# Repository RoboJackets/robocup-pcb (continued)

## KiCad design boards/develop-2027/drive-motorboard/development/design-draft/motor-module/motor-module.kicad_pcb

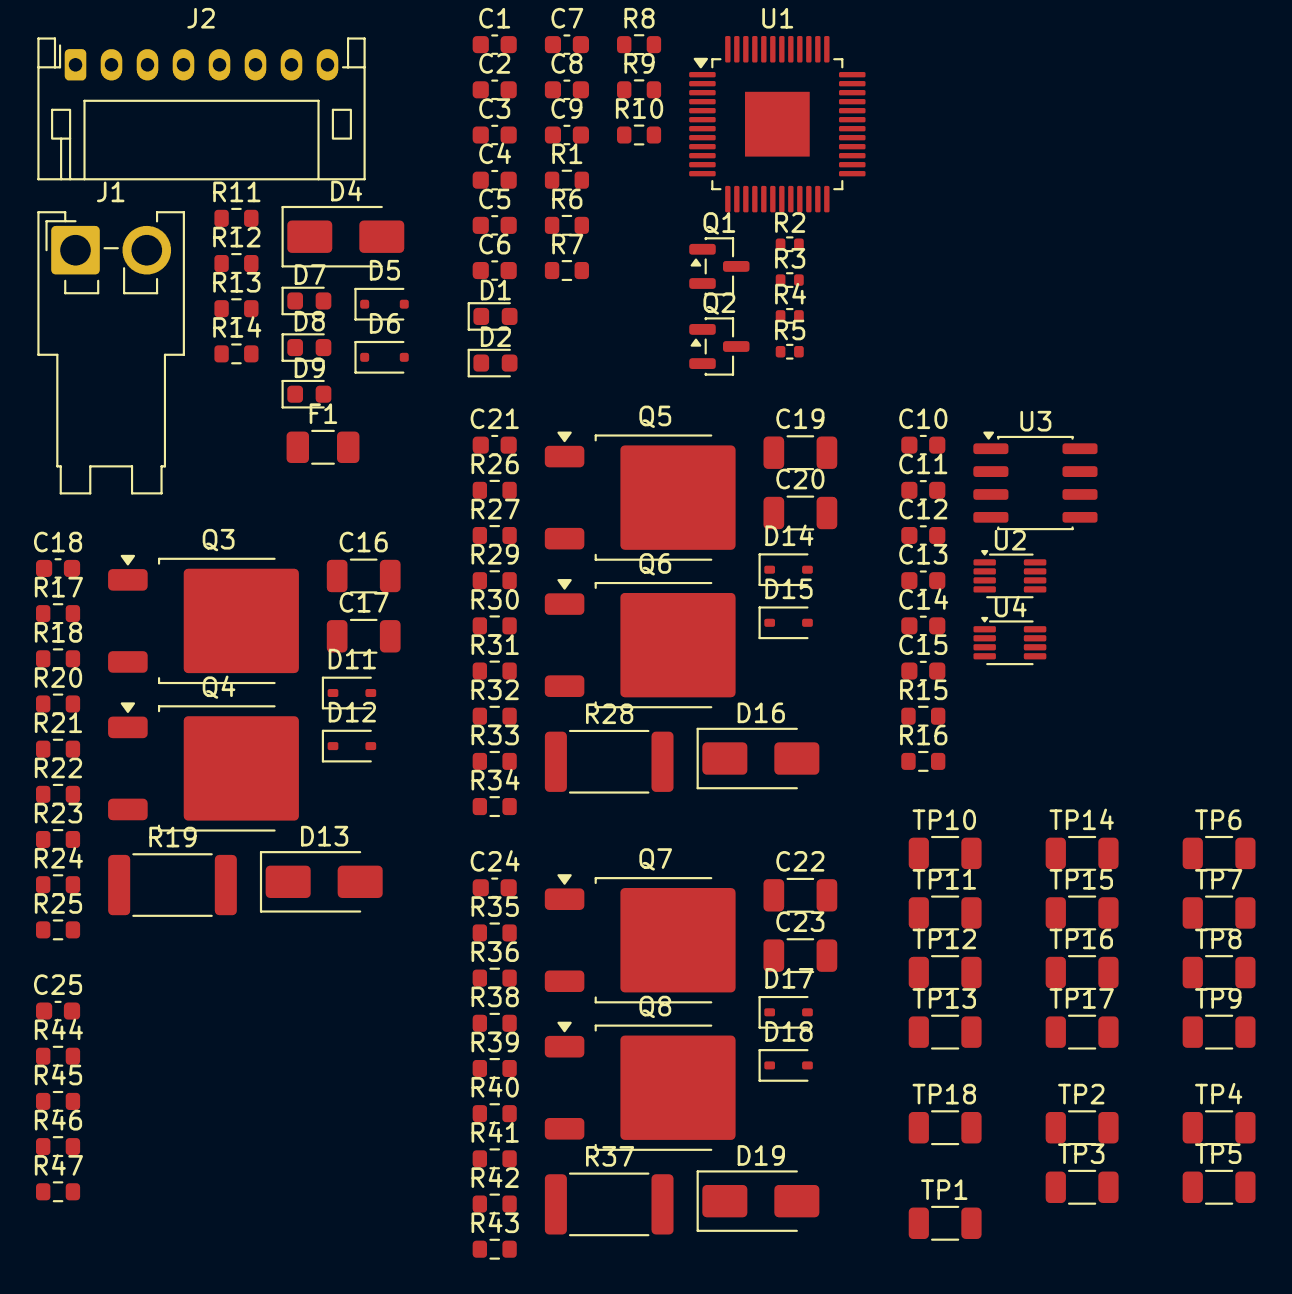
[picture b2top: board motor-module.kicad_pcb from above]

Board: 2 copper layers, 122 parts (0 on the bottom side), 74 nets, no tracks yet.

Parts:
C1, C4, C12, C13, C15: 100n; C_0603_1608Metric
C2, C5, C6, C7, C8, C9: 10u; C_0603_1608Metric
C3, C14: 1u; C_0603_1608Metric
C10, C11: 0.1n; C_0603_1608Metric
C16, C17, C19, C20, C22, C23: 10u; C_1206_3216Metric
C18, C21, C24, C25: 1n; C_0603_1608Metric
D1: FAULT; LED_0603_1608Metric
D2: DEBUG; LED_0603_1608Metric
D4, D13, D16, D19: SMAJ24CA; D_SMA
D5, D6: CUZ5V6,H3F; D_SOD-323F
D7: VDC OK; LED_0603_1608Metric
D8: 5V OK; LED_0603_1608Metric
D9: 3.3V OK; LED_0603_1608Metric
D11, D12, D14, D15, D17, D18: 1N4148WS; D_SOD-323
F1: 12 A 50 V; Fuse_1206_3216Metric
J1: Motor Power In; JST_VH_S2P-VH_1x02_P3.96mm_Horizontal
J2: Logical Conn.; JST_PH_S8B-PH-K_1x08_P2.00mm_Horizontal
Q1, Q2: BSS84AKW,115; SOT-23
Q3, Q4, Q5, Q6, Q7, Q8: STD140N6F7; TO-252-2
R1, R6, R7, R8: 10k; R_0603_1608Metric
R2, R3, R4, R5: 100; R_0402_1005Metric
R9, R10, R11, R12, R13, R14: 1k; R_0603_1608Metric
R15, R16, R17, R18, R25, R26, R27, R34, R35, R36, R43: 100; R_0603_1608Metric
R19, R28, R37: 5m±1% 3W; R_2512_6332Metric
R20, R23, R29, R32, R38, R41: 110±0.1%; R_0603_1608Metric
R21, R22, R30, R31, R39, R40: 6.04k±0.1%; R_0603_1608Metric
R24, R33, R42: 3.01k±0.1%; R_0603_1608Metric
R44, R45, R46: 3.3k; R_0603_1608Metric
R47: 15k; R_0603_1608Metric
TP1: RESET; R_1206_3216Metric
TP2: 5V; R_1206_3216Metric
TP3: 3.3V; R_1206_3216Metric
TP4: ENC_A; R_1206_3216Metric
TP5: ENC_B; R_1206_3216Metric
TP6, TP10, TP14: HS_x; R_1206_3216Metric
TP7, TP11, TP15: LS_x; R_1206_3216Metric
TP8, TP12, TP16: PHASE_x; R_1206_3216Metric
TP9, TP13, TP17: ISENSE_x; R_1206_3216Metric
TP18: OCCOMP; R_1206_3216Metric
U1: STSPIN32G0A2; LQFP-48-1EP_7x7mm_P0.5mm_EP3.6x3.6mm
U2, U4: SN74LVC3G17DCUR; VSSOP-8_2.3x2mm_P0.5mm
U3: SN75157DR; SOIC-8_3.9x4.9mm_P1.27mm

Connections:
+3.3V: C2.2, C3.2, C4.2, C12.1, C15.1, D6.1 (A1), J2.3, Q1.3 (D), Q2.3 (D), R1.1, R7.2, R8.2, R14.1, R21.2, R30.2, R39.2, R47.2, TP3.1, U1.5 (V_{DD}), U2.8 (Vcc), U4.8 (Vcc)
+5V: C13.1, C14.1, D5.1 (A1), J2.1, R13.1, TP2.1, U3.8 (Vcc)
/ENC_A: TP4.1, U1.43 (PB6), U4.7 (1Y)
/ENC_B: TP5.1, U1.45 (PB7), U4.5 (2Y)
/H1: U1.15 (PA3), U2.7 (1Y)
/H2: U1.16 (PA4), U2.5 (2Y)
/H3: U1.17 (PA5), U2.2 (3Y)
/Microcontroller/DEBUG: Q2.1 (G), R7.1, U1.10 (PF0)
/Microcontroller/FAULT: Q1.1 (G), R6.1, U1.1 (PC14)
/Microcontroller/HS_U: D11.1 (K), R17.1, TP6.1, U1.34 (HSU)
/Microcontroller/HS_V: D14.1 (K), R26.1, TP10.1, U1.30 (HSV)
/Microcontroller/HS_W: D17.1 (K), R35.1, TP14.1, U1.26 (HSW)
/Microcontroller/ISENSE_U: R24.2, R25.2, TP9.1, U1.12 (PA0), U1.22 (OP1O)
/Microcontroller/ISENSE_V: R33.2, R34.2, TP13.1, U1.4 (OP2O), U1.20 (PA7)
/Microcontroller/ISENSE_W: R42.2, R43.2, TP17.1, U1.21 (PB1), U1.48 (OP3O)
/Microcontroller/LS_U: D12.1 (K), R18.1, TP7.1, U1.37 (LSU)
/Microcontroller/LS_V: D15.1 (K), R27.1, TP11.1, U1.33 (LSV)
/Microcontroller/LS_W: D18.1 (K), R36.1, TP15.1, U1.29 (LSW)
/Microcontroller/OP_U_N: R23.2, R24.1, U1.23 (OP1N)
/Microcontroller/OP_U_P: R20.2, R21.1, R22.2, U1.24 (OP1P)
/Microcontroller/OP_V_N: R32.2, R33.1, U1.3 (OP2N)
/Microcontroller/OP_V_P: R29.2, R30.1, R31.2, U1.2 (OP2P)
/Microcontroller/OP_W_N: R41.2, R42.1, U1.47 (OP3N)
/Microcontroller/OP_W_P: R38.2, R39.1, R40.2, U1.46 (OP3P)
/Microcontroller/SPI1_CE_USART2_RX: J2.8, R5.1
/Microcontroller/SPI1_MISO: J2.7, R4.1
/Microcontroller/SPI1_MOSI_USART2_TX: J2.6, R3.1
/Microcontroller/SPI1_SCK: J2.5, R2.1
/Microcontroller/~RESET: R8.1, TP1.1, U1.11 (~RST)
/Motor Interface/EN_CH_A: R15.1, U3.1 (1IN+)
/Motor Interface/EN_CH_B: R16.1, U3.6 (2IN+)
/Motor Interface/~EN_CH_A: C10.2, U3.7 (1IN-)
/Motor Interface/~EN_CH_B: C11.2, U3.5 (2IN-)
/OCCOMP: C25.1, R44.2, R45.2, R46.2, R47.1, TP18.1, U1.25 (OCCOMP)
/PHASE_U: C7.1, D13.2 (A2), Q3.3, Q4.1, TP8.1, U1.35 (OUTU)
/PHASE_V: C8.1, D16.2 (A2), Q5.3, Q6.1, TP12.1, U1.31 (OUTV)
/PHASE_W: C9.1, D19.2 (A2), Q7.3, Q8.1, TP16.1, U1.27 (OUTW)
/SHUNT_U: Q4.3, R19.1, R20.1, R44.1
/SHUNT_V: Q6.3, R28.1, R29.1, R45.1
/SHUNT_W: Q8.3, R37.1, R38.1, R46.1
GND: C1.2, C2.1, C3.1, C4.1, C5.1, C6.2, C12.2, C13.2, C14.2, C15.2, C16.2, C17.2, C18.1, C19.2, C20.2, C21.1, C22.2, C23.2, C24.1, C25.2, D1.1 (K), D2.1 (K), D4.1 (A1), D5.2 (A2), D6.2 (A2), D7.1 (K), D8.1 (K), D9.1 (K), D13.1 (A1), D16.1 (A1), D19.1 (A1), J1.2, J2.2, J2.4, R6.2, R19.2, R22.1, R23.1, R28.2, R31.1, R32.1, R37.2, R40.1, R41.1, U1.19 (TESTMODE), U1.44 (GND), U1.49 (GND_PAD), U2.4 (GND), U3.4 (GND), U4.4 (GND)
unnamed: C10.1, R15.2
unnamed: C11.1, R16.2
unnamed: C18.2, R25.1
unnamed: C21.2, R34.1
unnamed: C24.2, R43.1
unnamed: D1.2 (A), R9.2
unnamed: D2.2 (A), R10.2
unnamed: D7.2 (A), R12.2
unnamed: D8.2 (A), R13.2
unnamed: D9.2 (A), R14.2
unnamed: D11.2 (A), Q3.2, R17.2
unnamed: D12.2 (A), Q4.2, R18.2
unnamed: D14.2 (A), Q5.2, R26.2
unnamed: D15.2 (A), Q6.2, R27.2
unnamed: D17.2 (A), Q7.2, R35.2
unnamed: D18.2 (A), Q8.2, R36.2
unnamed: F1.1, J1.1
unnamed: Q1.2 (S), R9.1
unnamed: Q2.2 (S), R10.1
unnamed: R11.2, R12.1
unnamed: R2.2, U1.13 (PA1)
unnamed: R3.2, U1.14 (PA2)
unnamed: R4.2, U1.18 (PA6)
unnamed: R5.2, U1.42 (PA15)
unnamed: C6.1, U1.9 (REG_3V3)
unnamed: C5.2, U1.6 (REG_12V)
unnamed: C7.2, U1.36 (VBOOTU)
unnamed: C8.2, U1.32 (VBOOTV)
unnamed: C9.2, U1.28 (VBOOTW)
unnamed: C1.1, R1.2, U1.38 (~STBY)
unnamed: U3.2 (1OUT), U4.1 (1A)
unnamed: U3.3 (2OUT), U4.3 (2A)
VDC: C16.1, C17.1, C19.1, C20.1, C22.1, C23.1, D4.2 (A2), F1.2, Q3.1, Q5.1, Q7.1, R11.1, U1.7 (VM)

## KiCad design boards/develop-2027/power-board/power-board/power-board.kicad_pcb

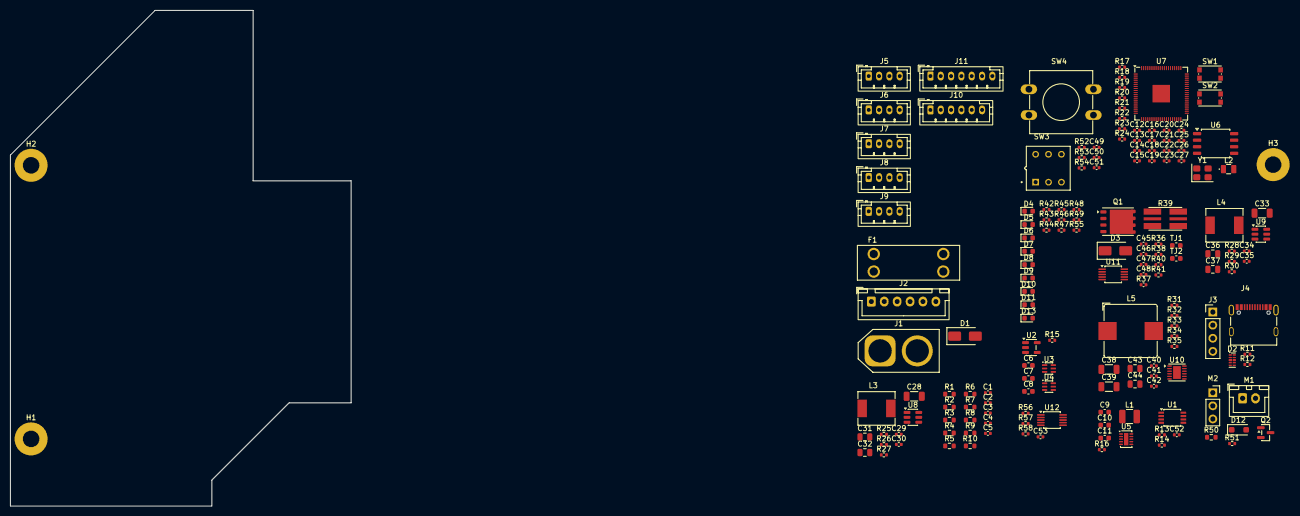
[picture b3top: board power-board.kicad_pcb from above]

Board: 4 copper layers, 66.0 x 96.0 mm, 167 parts (0 on the bottom side), 100 nets, no tracks yet.

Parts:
C1, C2, C3, C4, C5, C12, C15, C16, C18, C20, C21, C22, C23, C25, C26, C27, C49, C50, C51, C52, C53: 100n; C_0402_1005Metric
C6, C9: 1u 63V; C_0603_1608Metric
C7: 1u 25V; C_0603_1608Metric
C8, C10, C11: 10u 25V; C_0603_1608Metric
C13, C14: 15p; C_0402_1005Metric
C17, C19, C24: 4.7u; C_0402_1005Metric
C28, C33, C38, C39: 4.7u 50V; C_1206_3216Metric
C29, C34, C40, C45, C47: 100n 50V; C_0402_1005Metric
C30, C35, C41: 100n 16V; C_0402_1005Metric
C31, C32, C36, C37, C43, C44: 10u 25V; C_0805_2012Metric
C42: 33p; C_0402_1005Metric
C46, C48: 1n; C_0402_1005Metric
D1, D3: SMAJ22CA; D_SMA
D2: PUSB3FR4Z; Diodes_UDFN-10_1x2.5mm_P0.5mm
D4, D5, D6, D7, D8, D9, D10, D11, D13: KT-0603R; LED_0603_1608Metric
D12: SMD110PL-TP; D_SOD-123F
F1: Fuse Holder; Fuseholder_Keystone_3557-2
H1, H2, H3: MountingHole_Pad; MountingHole_3.2mm_M3_Pad
J1: XT60-M; AMASS_XT60-M_1x02_P7.20mm_Vertical
J2: B6B-XH-A; JST_XH_B6B-XH-A_1x06_P2.50mm_Vertical
J3: SWD; PinHeader_1x04_P2.54mm_Vertical
J4: 12402012E212A; USB_C_Receptable_Amphenol_12402012E212A
J5, J6, J7, J8, J9: B4B-PH-K-S; JST_PH_B4B-PH-K_1x04_P2.00mm_Vertical
J10: B6B-PH-K-S; JST_PH_B6B-PH-K_1x06_P2.00mm_Vertical
J11: B7B-PH-K-S; JST_PH_B7B-PH-K_1x07_P2.00mm_Vertical
L1: 10u 540mA; L_1210_3225Metric
L2: 3.3u 2.3A; L_Abracon_AOTA-B201610S
L3: 5.6u 5.5A; L_Bourns_SRP6540
L4: 6.8u 5A; L_Bourns_SRP6540
L5: 6.8u 8A; L_Bourns_SRP1038C_10.0x10.0mm
M1: B2B-XH-A; JST_XH_B2B-XH-A_1x02_P2.50mm_Vertical
M2: Motor_Servo; PinSocket_1x03_P2.54mm_Vertical
Q1: BSC014N06NS; Infineon_PG-TDSON-8_6.15x5.15mm
Q2: 2N7002K; SOT-23
R1: 180k ± 1%; R_0603_1608Metric
R2, R4, R6, R8, R10: 330k ± 1%; R_0603_1608Metric
R3: 1.8M ± 1%; R_0603_1608Metric
R5: 680k ± 1%; R_0603_1608Metric
R7: 2.2M ± 1%; R_0603_1608Metric
R9: 1.2M ± 1%; R_0603_1608Metric
R11, R12: 5.1k; R_0402_1005Metric
R13, R14, R56, R57, R58: 4.7k; R_0402_1005Metric
R15, R20, R21, R22, R35, R41, R42, R43, R44, R45, R46, R47, R48, R49, R53, R55: 1k; R_0402_1005Metric
R16, R23, R24, R25, R28, R31, R36, R51, R52, R54: 100k; R_0402_1005Metric
R17, R18: 27.4; R_0402_1005Metric
R19: 33; R_0402_1005Metric
R26, R29, R33: 100k ± 1%; R_0402_1005Metric
R27: 22.1k ± 1%; R_0402_1005Metric
R30: 13.7k ± 1%; R_0402_1005Metric
R32: 31.6k ± 1%; R_0402_1005Metric
R34: 7.15k ± 1%; R_0402_1005Metric
R37: 41.2k; C_0402_1005Metric
R38: 5.23k; R_0402_1005Metric
R39: 1.5m ± 1% 2W; R_Shunt_Analog_2512_6332_HighAccuracy
R40: 10; R_0402_1005Metric
R50: 100; R_0603_1608Metric
SW1: BOOTSEL; SW_Push_1P1T_NO_CK_KMR2
SW2: RESET; SW_Push_1P1T_NO_CK_KMR2
SW3: TL2201EEYB; SW_E-Switch_TL2201_DPDT
SW4: TL1100F160Q6JBLK; SW_PUSH-12mm
TJ1, TJ2: THJP0603AST1; C_0603_1608Metric
U1: LM75ADP; TSSOP-8_3x3mm_P0.65mm
U2: TLV75533PDBVR; SOT-23-5
U3, U4: LM66100DCK; SOT-363_SC-70-6
U5: TPS62177DQC; WSON-10-1EP_2x3mm_P0.5mm_EP0.84x2.4mm
U6: W25Q16JVSS; SOIC-8_5.3x5.3mm_P1.27mm
U7: RP2350B; QFN-80-1EP_10x10mm_P0.4mm_EP3.4x3.4mm
U8, U9: LMR51430X; SOT-23-6
U10: LMR51450; WSON-12-1EP_3x3mm_P0.5mm_EP1.5x2.5mm
U11: TPS2491DGS; TSSOP-10_3x3mm_P0.5mm
U12: INA226; TSSOP-10_3x3mm_P0.5mm
Y1: ABM8-272-T3; Crystal_SMD_Abracon_ABM8G-4Pin_3.2x2.5mm

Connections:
+1.1V: C15.1, C16.1, C18.1, C24.1, L2.1, U7.10 (DVDD), U7.32 (DVDD), U7.51 (DVDD), U7.65 (VREG_FB)
+3.3V: C8.1, C12.1, C19.1, C20.1, C21.1, C22.1, C23.1, C25.1, C26.1, C27.1, C52.1, C53.1, J3.1, R13.1, R14.1, R19.1, R23.2, R24.2, R56.1, R57.1, R58.1, SW3.6 (C), SW4.1, U1.8 (VCC), U3.6 (VOUT), U4.6 (VOUT), U6.8 (VCC), U7.5 (IOVDD), U7.15 (IOVDD), U7.24 (IOVDD), U7.29 (IOVDD), U7.41 (IOVDD), U7.50 (IOVDD), U7.59 (ADC_AVDD), U7.60 (IOVDD), U7.64 (VREG_VIN), U7.68 (USB_OTP_VDD), U7.69 (QSPI_IOVDD), U7.76 (IOVDD), U12.6 (VS)
/Battery Connectors/Batt_Balance.Cell0: C1.1, R1.2, R2.1, U7.54 (GPIO43/ADC3)
/Battery Connectors/Batt_Balance.Cell1: C3.1, R5.2, R6.1, U7.55 (GPIO44/ADC4)
/Battery Connectors/Batt_Balance.Cell2: C5.1, R9.2, R10.1, U7.56 (GPIO45/ADC5)
/Battery Connectors/Batt_Balance.Cell3: C2.1, R3.2, R4.1, U7.58 (GPIO47/ADC7)
/Battery Connectors/Batt_Balance.Cell4: C4.1, R7.2, R8.1, U7.57 (GPIO46/ADC6)
/Battery Connectors/Batt_Cell0: J2.5, R1.1
/Battery Connectors/Batt_Cell1: J2.4, R5.1
/Battery Connectors/Batt_Cell2: J2.3, R9.1
/Battery Connectors/Batt_Cell3: J2.2, R3.1
/Battery Connectors/Batt_Cell4: J2.1, R7.1
/Battery Connectors/VBATT: C9.1, C45.1, D1.1 (A1), F1.2, R39.3, R39.4, TJ1.1 (Pin1), U5.2 (VIN), U5.3 (EN), U11.10 (VCC), U12.10 (Vin+)
/MCU Connectors/CC1: J4.B5 (CC1_B), R11.1
/MCU Connectors/CC2: J4.A5 (CC1_A), R12.1
/MCU Connectors/CLK: J3.3, U7.33 (SWCLK)
/MCU Connectors/DN: D2.1 (CH1), J4.A7 (D-_A), J4.B7 (D-_B), R17.1
/MCU Connectors/DP: D2.5 (CH4), J4.A6 (D+_A), J4.B6 (D+_B), R18.1
/MCU Connectors/IO: J3.2, U7.34 (SWDIO)
/MCU Power/3.3V_MCU_BUCK: C10.1, C11.1, L1.2, R15.1, R16.1, U3.1 (VIN), U5.8 (~SLEEP), U5.10 (VOS)
/MCU Power/3.3V_USB: C7.1, U2.5 (OUT), U3.3 (~CE), U4.1 (VIN)
/MCU/3.3V_EN: R25.1, U7.25 (GPIO24), U8.5 (EN)
/MCU/5.0V_EN: R28.1, U7.23 (GPIO23), U9.5 (EN)
/MCU/12.0V_EN: R31.1, U7.22 (GPIO22), U10.9 (EN)
/MCU/CURR_ALERT: R58.2, U7.11 (GPIO12), U12.3 (~Alert)
/MCU/ESTOP: C51.1, R52.1, SW3.5 (B), U7.13 (GPIO14)
/MCU/FAN_PWM: R50.1, U7.9 (GPIO11)
/MCU/IND_3.3V_EN: D7.2 (A), U7.80 (GPIO3)
/MCU/IND_5V_EN: D6.2 (A), U7.79 (GPIO2)
/MCU/IND_12V_EN: D5.2 (A), U7.78 (GPIO1)
/MCU/IND_COOL_CH1: D8.2 (A), U7.1 (GPIO4)
/MCU/IND_COOL_CH2: D9.2 (A), U7.2 (GPIO5)
/MCU/IND_ESTOP: D10.2 (A), U7.7 (GPIO9)
/MCU/IND_OVERTEMP: D11.2 (A), U7.4 (GPIO7)
/MCU/IND_SYSTEM: D13.2 (A), U7.6 (GPIO8)
/MCU/IND_VBATT_EN: D4.2 (A), U7.77 (GPIO0)
/MCU/POWERSW: C49.1, R53.2, U7.12 (GPIO13)
/MCU/QSPI_CLK: U6.6 (CLK), U7.71 (QSPI_SCLK)
/MCU/QSPI_SD0: U6.5 (DI/IO_{0}), U7.72 (QSPI_SD0)
/MCU/QSPI_SD1: U6.2 (DO/IO_{1}), U7.74 (QSPI_SD1)
/MCU/QSPI_SD2: U6.3 (~WP/IO_{2}), U7.73 (QSPI_SD2)
/MCU/QSPI_SD3: U6.7 (~HOLD/~RESET/IO_{3}), U7.70 (QSPI_SD3)
/MCU/RX: J11.1, U7.19 (GPIO19)
/MCU/SCL: R14.2, R57.2, U1.2 (SCL), U7.17 (GPIO17), U7.28 (GPIO27), U12.5 (SCL)
/MCU/SDA: R13.2, R56.2, U1.1 (SDA), U7.16 (GPIO16), U7.27 (GPIO26), U12.4 (SDA)
/MCU/SERVO_PWM: M2.1 (PWM), U7.8 (GPIO10)
/MCU/TX: J11.2, U7.18 (GPIO18)
/MCU/VBATT_EN: SW3.1 (A), U7.26 (GPIO25)
/MCU/~BOOTSEL: R21.2, R23.1, U6.1 (~CS), U7.75 (~QSPI_SS)
/MCU/~RESET: R22.2, R24.1, U7.35 (RUN)
/Output Connectors/3.3V_REG: C31.1, C32.1, J11.4, L3.2, R26.1
/Output Connectors/5.0V_REG: C36.1, C37.1, D12.1 (K), J11.6, L4.2, M1.1 (+), M2.2 (+), R29.1
/Output Connectors/12.0V_REG: C43.1, C44.1, J10.4, J10.5, J10.6, L5.2, R33.1, R35.1
/Output Power Stage/25V, 30A Load Switch/SHUNT_L: Q1.5 (D), R39.1, R39.2, U11.9 (SENSE), U12.8 (Vbus), U12.9 (Vin-)
/Output Power Stage/LOADSW_EN: C50.1, R36.1, SW3.2 (B), U11.1 (EN)
GND: C1.2, C2.2, C3.2, C4.2, C5.2, C6.2, C7.2, C8.2, C9.2, C10.2, C11.2, C12.2, C13.1, C14.1, C15.2, C16.2, C17.2, C18.2, C19.2, C20.2, C21.2, C22.2, C23.2, C24.2, C25.2, C26.2, C27.2, C28.2, C29.2, C31.2, C32.2, C33.2, C34.2, C36.2, C37.2, C38.2, C39.2, C40.2, C42.2, C43.2, C44.2, C45.2, C46.2, C47.2, C48.2, C49.2, C50.2, C51.2, C52.2, C53.2, D1.2 (A2), D2.3 (GND), D2.8 (GND), D3.2 (A2), H1.1 (1_1), H2.1 (1_1), H3.1 (1_1), J1.1, J2.6, J3.4, J4.A1_B12 (GND), J4.B1_A12 (GND), J4.SH1 (SHIELD), J4.SH2 (SHIELD), J4.SH3 (SHIELD), J4.SH4 (SHIELD), J5.1, J5.2, J6.1, J6.2, J7.1, J7.2, J8.1, J8.2, J9.1, J9.2, J10.1, J10.2, J10.3, J11.3, J11.5, J11.7, M2.3 (-), Q2.2 (S), R2.2, R4.2, R6.2, R8.2, R10.2, R11.2, R12.2, R25.2, R27.2, R28.2, R30.2, R31.2, R32.2, R34.2, R36.2, R38.2, R42.2, R43.2, R44.2, R45.2, R46.2, R47.2, R48.2, R49.2, R51.2, R52.2, R54.2, R55.2, SW1.1 (A), SW2.1 (A), SW3.3 (C), SW3.4 (A), TJ1.2 (Pin2), TJ2.1 (Pin1), U1.4 (GND), U1.5 (A2), U1.6 (A1), U1.7 (A0), U2.2 (GND), U3.2 (GND), U4.2 (GND), U4.5 (ST), U5.1 (PGND), U5.4 (NC), U5.5 (FB), U5.6 (AGND), U5.11 (PAD), U6.4 (GND), U7.62 (VREG_PGND), U7.81 (GND), U8.1 (GND), U9.1 (GND), U10.5 (PG), U10.8 (AGND), U10.13 (PGND), U11.5 (GND), U11.6 (PG), U12.1 (A1), U12.2 (A0), U12.7 (GND), Y1.2 (G), Y1.4 (G)
unnamed: C14.2, R20.1, Y1.3
unnamed: C41.2, L5.1, U10.1 (SW), U10.2 (SW), U10.3 (SW)
unnamed: C42.1, R35.2
unnamed: C48.1, R41.2
unnamed: D4.1 (K), R42.1
unnamed: D5.1 (K), R43.1
unnamed: D6.1 (K), R44.1
unnamed: D7.1 (K), R45.1
unnamed: D8.1 (K), R46.1
unnamed: D9.1 (K), R47.1
unnamed: D10.1 (K), R48.1
unnamed: D11.1 (K), R49.1
unnamed: D12.2 (A), M1.2 (-), Q2.3 (D)
unnamed: D13.1 (K), R55.1
unnamed: F1.1, J1.2
unnamed: Q1.4 (G), R40.1
unnamed: Q2.1 (G), R50.2, R51.1
unnamed: R53.1, R54.1, SW4.2
unnamed: R21.1, SW1.2 (B)
unnamed: R22.1, SW2.2 (B)
unnamed: R15.2, U3.5 (ST), U4.3 (~CE)
unnamed: R16.2, U5.7 (PG)
unnamed: L1.1, U5.9 (SW)
unnamed: R17.2, U7.66 (USB_DM)
unnamed: R18.2, U7.67 (USB_DP)
unnamed: C17.1, R19.2, U7.61 (VREG_AVDD)
unnamed: L2.2, U7.63 (VREG_LX)
unnamed: C13.2, U7.30 (XIN), Y1.1
unnamed: R20.2, U7.31 (XOUT)
unnamed: C30.1, U8.6 (CB)
unnamed: R26.2, R27.1, U8.4 (FB)
unnamed: C30.2, L3.1, U8.2 (SW)
unnamed: C35.1, U9.6 (CB)
unnamed: R29.2, R30.1, U9.4 (FB)
unnamed: C35.2, L4.1, U9.2 (SW)
unnamed: C41.1, U10.4 (BOOT)
unnamed: R33.2, R34.1, U10.7 (FB)
unnamed: R32.1, U10.6 (RT)
unnamed: R40.2, R41.1, U11.8 (GATE)
unnamed: R37.2, R38.1, U11.3 (PROG)
unnamed: C46.1, U11.4 (TIMER)
unnamed: R37.1, U11.2 (VREF)
VBUS: C6.1, J4.A4_B9 (VBUS), J4.B4_A9 (VBUS), U2.1 (IN), U2.3 (EN)
VIN: C28.1, C29.1, C33.1, C34.1, C38.1, C39.1, C40.1, C47.1, D3.1 (A1), J5.3, J5.4, J6.3, J6.4, J7.3, J7.4, J8.3, J8.4, J9.3, J9.4, Q1.1 (S), Q1.2 (S), Q1.3 (S), TJ2.2 (Pin2), U8.3 (VIN), U9.3 (VIN), U10.10 (VIN), U10.11 (VIN), U10.12 (VIN), U11.7 (OUT)

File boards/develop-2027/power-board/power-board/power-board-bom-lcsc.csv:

"Reference","Qty","Value","Manufacturer P/N","Vendor","Vendor P/N"
"SW1","1","BOOTSEL","KMR211G LFS","LCSC","C99271"
"SW2","1","RESET","KMR211G LFS","LCSC","C99271"
"C1,C2,C3,C4,C5,C12,C15,C16,C18,C20,C21,C22,C23,C25,C26,C27","16","100n","GCM155R71H104KE02D","LCSC","C85858"
"C13,C14","2","15p","GJM1555C1H150GB01D","LCSC","C440152"
"C17,C19,C24","3","4.7u","GRM155R60J475ME47D","LCSC","C82453"
"C29,C34,C40,C45,C47","5","100n 50V","GCM155R71H104KE02D","LCSC","C85858"
"C30,C35,C41","3","100n 16V","GCM155R71H104KE02D","LCSC","C85858"
"C42","1","33p","GCM1555C1H330JA16D","LCSC","C126506"
"C46,C48","2","1n","GCM155R71H102KA37D","LCSC","C126532"
"R37","1","41.2k","0402WGF4122TCE","LCSC","C26978"
"C6,C9","2","1u 63V","CL10B105KB8NQNC","LCSC","C5199872"
"C7","1","1u 25V","CL10B105KB8NQNC","LCSC","C5199872"
"C8,C10,C11","3","10u 25V","GRM188R6YA106MA73D","LCSC","C91606"
"C31,C32,C36,C37","4","10u 16V","GRM21BR61E106MA73L","LCSC","C15850"
"C43,C44","2","10u 25V","GRM21BR61E106MA73L","LCSC","C15850"
"C28,C33,C38,C39","4","4.7u 50V","GRM31CR71H475KA12L","LCSC","C77096"
"J1","1","XT60-M","XT60-M.","LCSC","C98733"
"J5,J6,J7,J8,J9","5","B4B-PH-K-S","B4B-PH-K-S","LCSC","C131334"
"J10","1","B6B-PH-K-S","B6B-PH-K-S","LCSC","C131342"
"J11","1","B7B-PH-K-S","C157981","LCSC","C157981"
"J13","1","B2B-XH-A","B2B-XH-A","LCSC","C158012"
"J2","1","B6B-XH-A","B6B-XH-A","LCSC","C144397"
"Y1","1","ABM8-272-T3","ABM8-272-T3","LCSC","C20625731"
"D1,D3","2","SMAJ22CA","SMAJ22CA","LCSC","C148221"
"D12","1","SMD110PL-TP","SMD110PL-TP","LCSC","C669053"
"L1","1","10u 540mA","LBC3225T100KR","LCSC","C223424"
"L5","1","6.8u 8A","SRP1038A-6R8M","LCSC","C2047223"
"D4,D5,D6,D7,D8,D9,D10,D11","8","KT-0603R","KT-0603R","LCSC","C2286"
"D2","1","PUSB3FR4Z","PUSB3FR4Z","LCSC","C503418"
"U7","1","RP2350B","RP2350B","LCSC","C42415655"
"U6","1","W25Q16JVSS","W25Q16JVSSIQ","LCSC","C131025"
"U11","1","TPS2491DGS","TPS2491DGS","LCSC","C273636"
"U1","1","LM75ADP","LM75ADP,118","LCSC","C843694"
"Q1","1","BSC014N06NS","BSC014N06NSATMA1","LCSC","C113391"
"U5","1","TPS62177DQC","TPS62177DQC","LCSC","C91241"
"U10","1","LMR51450","LMR51450FNDRRR","LCSC","C5782413"
"Q2","1","2N7002K","2N7002K-TP","LCSC","C77975"
"U2","1","TLV75533PDBVR","TLV75533PDBVR","LCSC","C404027"
"U8,U9","2","LMR51430X","LMR51430XDDCR","LCSC","C5185863"
"U3,U4","2","LM66100DCK","LM66100DCKR","LCSC","C2869734"
"R11,R12","2","5.1k","RC0402FR-075K1L","LCSC","C105872"
"R13,R14","2","4.7k","RC0402FR-074K7L","LCSC","C105871"
"R15,R20,R21,R22,R35,R41,R42,R43,R44,R45,R46,R47,R48,R49","14","1k","RC0402FR-071KL","LCSC","C106235"
"R16,R23,R24,R25,R28,R31,R36,R51","8","100k","RC0402FR-07100KL","LCSC","C60491"
"R17,R18","2","27.4","RC0402FR-0727R4L","LCSC","C3951825"
"R19","1","33","RC0402JR-0733RL","LCSC","C137880"
"R26,R29,R33","3","100k ± 1%","RC0402FR-07100KL","LCSC","C60491"
"R27","1","22.1k ± 1%","RMCF0402FT22K1","LCSC","C226356"
"R30","1","13.7k ± 1%","RC0402FR-0713K7L","LCSC","C274888"
"R32","1","31.6k ± 1%","RC0402FR-0731K6L","LCSC","C11463"
"R34","1","7.15k ± 1%","RC0402FR-077K15L","LCSC","C409927"
"R38","1","5.23k","RC-02K243JT","LCSC","C1152"
"R40","1","10","RC0402FR-0710RL","LCSC","C138066"
"R1","1","180k ± 1%","CR0603-FX-1803ELF","LCSC","C123419"
"R2,R4,R6,R8,R10","5","330k ± 1%","MCR03SEQPF3303","LCSC","C114618"
"R3","1","1.8M ± 1%","RC0603FR-071M8L","LCSC","C13318"
"R5","1","680k ± 1%","MCR03SEQPF6803","LCSC","C137690"
"R7","1","2.2M ± 1%","RC0603FR-072M2L","LCSC","C22938"
"R9","1","1.2M ± 1%","RC0603FR-131M2L","LCSC","C137774"
"R50","1","100","CRCW0603100RFKEA","LCSC","C844917"
"J4","1","12402012E212A","12402012E212A","LCSC","C5150972"
"L2","1","3.3u 2.3A","AOTA-B201610S3R3-101-T","LCSC","C42411119"
"L3","1","5.6u 5.5A","SRP6540-5R6M","LCSC","C2041376"
"L4","1","6.8u 5A","SRP6540-6R8M","LCSC","C2041325"
"R39","1","1.5m ± 1% 2W","PA2512FKF7W1U5E","LCSC","C7023721"

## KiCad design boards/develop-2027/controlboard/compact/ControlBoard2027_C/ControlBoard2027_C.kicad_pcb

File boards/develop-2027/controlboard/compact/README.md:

# Compact board set (ControlBoard2027_C + 30 x 40 radio)

The compact set is the active 2027 robot electronics design: a 120 x 60 mm controlboard with an STM32H723 and a
30 x 40 mm ESP32-C5 radio that plugs straight onto it. It replaces the prototype set in `../prototype/` (kept for
reference only); every difference is listed in [docs/PROTOTYPE_TO_COMPACT.md](docs/PROTOTYPE_TO_COMPACT.md).

| Board | Folder | Size, layers | Main parts |
|---|---|---|---|
| ControlBoard2027_C | [ControlBoard2027_C/](ControlBoard2027_C/) | 120 x 60 mm, 6 layers, JLC06161H-3313E 1.6 mm | STM32H723ZGT6, LSM6DSV320X IMU, microSD, USB-C, 4 motor + dribbler SPI ports, kicker / expansion I2C, powerboard input, DotStar LEDs, OLED socket |
| RadioBoard2027_C_Inboard | [RadioBoard2027_C_Inboard/](RadioBoard2027_C_Inboard/) | 30 x 40 mm, 4 layers, JLC04161H-3313 1.6 mm | ESP32-C5-WROOM-1U, USB-C, power mux + supervisor |
| RadioBoard2027_C_Overhang | [RadioBoard2027_C_Overhang/](RadioBoard2027_C_Overhang/) | 30 x 40 mm, 4 layers, JLC04161H-3313 1.6 mm | same circuit as Inboard |

## Which files are authoritative

1. The KiCad files in each board folder (`.kicad_sch`, `.kicad_pcb`, `.kicad_dru`, `lib/`, `footprints/`). They
   always win.
2. The documents below, which were checked against those files on 2026-11-07.

Positions in all documents are in mm from the top-left corner of the board's own outline, x right, y down. In the
board files that corner is at (49.475, 49.475) on the controlboard and (97.0, 100.0) on the radios.

| Document | For | Content |
|---|---|---|
| [docs/INTERFACE.md](docs/INTERFACE.md) | everyone | J9 / J2 board-to-board pin table, mating rule, positions, standoffs, stack height, keep-outs, link timing; controlboard external connector pinouts and what mating boards must use |
| [docs/FIRMWARE.md](docs/FIRMWARE.md) | firmware | STM32 and ESP32-C5 pin maps, clocks, GPIO speed rules, IMU orientation, power switchover, bring-up checklist |
| [docs/PROTOTYPE_TO_COMPACT.md](docs/PROTOTYPE_TO_COMPACT.md) | reviewers, firmware | every change from the prototype, part by part, with reasons |
| [ControlBoard2027_C/DESIGN_NOTES.md](ControlBoard2027_C/DESIGN_NOTES.md), [TODO.txt](ControlBoard2027_C/TODO.txt) | reviewers | controlboard design reasoning, stackup, lengths, rules, deviations; open items |
| [RadioBoard2027_C_Inboard/DESIGN_NOTES.md](RadioBoard2027_C_Inboard/DESIGN_NOTES.md), [TODO.txt](RadioBoard2027_C_Inboard/TODO.txt) | reviewers | Inboard radio design notes; open items |
| [RadioBoard2027_C_Overhang/DESIGN_NOTES.md](RadioBoard2027_C_Overhang/DESIGN_NOTES.md), [TODO.txt](RadioBoard2027_C_Overhang/TODO.txt) | reviewers | Overhang radio design notes; open items |

Diagrams:
- [docs/img/interface_stack.svg](docs/img/interface_stack.svg): the set from above, connectors, J9 pin map, stack;
- [docs/img/cb_compact_layout_top.svg](docs/img/cb_compact_layout_top.svg) and
  [docs/img/cb_compact_layout_bottom.svg](docs/img/cb_compact_layout_bottom.svg): controlboard placement by function;
- [RadioBoard2027_C_Inboard/docs/board_map.svg](RadioBoard2027_C_Inboard/docs/board_map.svg) and
  [RadioBoard2027_C_Overhang/docs/board_map.svg](RadioBoard2027_C_Overhang/docs/board_map.svg): radio buttons, LEDs,
  USB, test pads and the J2 pin map.

## BOM

The bills of materials are in each board's `bom/` folder: [ControlBoard2027_C/bom/](ControlBoard2027_C/bom/),
[RadioBoard2027_C_Inboard/bom/](RadioBoard2027_C_Inboard/bom/) and
[RadioBoard2027_C_Overhang/bom/](RadioBoard2027_C_Overhang/bom/). Each folder has a full BOM with sourcing and stock,
the JLCPCB upload file, a list of the parts to order separately (Digi-Key / Mouser), and a README with the stock date,
board-set limits, substitutions and open issues. The JLCPCB upload file is generated from the schematic fields.
The LDOs (CB U7, radio U4) are Microchip MCP1826S-3302E/DB (the AP7361C-33E-13 was out of stock everywhere on
2026-11-07). The LSHM mezzanine (CB J9, radio J2) is JLCPCB-assembled as C3643542: 37 at JLCPCB on 2026-11-07, two
per board set, so 18 board sets.

## Folder map

| Path | Content |
|---|---|
| `README.md` | this file |
| `docs/` | set-level documents; `docs/img/` their SVG diagrams |
| `ControlBoard2027_C/` | controlboard KiCad project, `DESIGN_NOTES.md`, `TODO.txt`, `lib/`, `footprints/` |
| `RadioBoard2027_C_Inboard/` | Inboard radio KiCad project, `DESIGN_NOTES.md`, `TODO.txt`, `docs/board_map.svg`, `lib/` |
| `RadioBoard2027_C_Overhang/` | Overhang radio KiCad project, `DESIGN_NOTES.md`, `TODO.txt`, `docs/board_map.svg`, `lib/` |

## The two radio variants

Both radios have the same schematic (identical netlists), the same outline, the same J2 position and pinout and the
same standoff holes, so either one fits the same controlboard. Both accept the ESP32-C5-WROOM-1U (primary build,
u.FL connector with an external antenna) and the ESP32-C5-WROOM-1 (fallback, PCB antenna) on one dual footprint.
They differ only in where the module sits, which matters only for a WROOM-1 build:

| | Inboard | Overhang |
|---|---|---|
| Module position | (19.85, 17.9), antenna end 1 mm inside the north edge | (19.85, 11.5), antenna end past the north edge |
| WROOM-1 antenna | inside the radio outline, over the controlboard (CB x 46.1-66.1, y 0-7.5, where the CB has copper) | 5.45 mm past the radio and controlboard front edge (keep-out 6.4 mm) |
| Link length on the radio (matched) | 19.934 mm | 14.079 mm |
| USB pair skew | orientation B -0.001 mm, A +5.94 mm (about 40 ps; a both-orientation match does not fit beside SW2; negligible at Full Speed; one-orientation match accepted per the user's instruction) | -0.001 / +0.000 mm in both orientations |
| Buttons | RESET on the west edge, BOOT on the south edge | RESET and BOOT side by side near the south edge |

With the WROOM-1U both variants work the same. Pick the Overhang if a WROOM-1 build is likely and the robot has room
in front of the board; pick the Inboard if nothing may stick out.

## Status (2026-11-07)

All three boards are placed and routed. Checks on the saved repo files (kicad-cli, schematic parity on, zones as
saved):

| Board | DRC errors | Unconnected | Parity | DRC warnings | ERC |
|---|---|---|---|---|---|
| ControlBoard2027_C | 0 | 0 | 0 | 13, all intended: 11 courtyard overlaps (J9 / U2 margin 0.02 mm; ten low parts under the raised OLED module J13) and 2 J2 locating holes under J13 | 1 error, intended: U2 VCAP pins 71 / 106 tied (power output to power output) |
| RadioBoard2027_C_Inboard | 0 | 0 | 0 | 0 | 0 |
| RadioBoard2027_C_Overhang | 0 | 0 | 0 | 0 | 0 |

Matched groups (re-measured with the length scripts on the saved boards):

| Group | Result |
|---|---|
| CB radio SPI3 (to J9) | 14.860-14.861 mm |
| CB SDMMC2 | 62.231-62.496 mm (D1 +0.264 mm, within 1 mm) |
| CB motor SPI1 / SPI2 / dribbler SPI4, LED SPI6 | each connector within 0.001 mm, except J6 MOSI -0.222 mm |
| CB USB | 0.000 mm skew in both plug orientations |
| Radio link SCK / MOSI / MISO / CS | Inboard 19.934 mm, Overhang 14.079 mm, spread 0.000 mm |
| Radio USB | see the variant table above |

Each board's independent adversarial audits are summarised in the Review history appendix of its DESIGN_NOTES.

### Open before ordering

Details and the full lists are in each board's TODO.txt.

- **All boards:** confirm the impedance widths in JLC's calculator and order with impedance control; independent
  re-audit of the last changed areas (CB back-edge connectors and audit fixes; Overhang USB-skew changes; Inboard
  after any further change), then refill zones, DRC with parity, ERC and the length scripts again; generate the
  placement files (the BOMs exist, see above); re-check stock (LSHM C3643542 is the limiting JLCPCB part); parts not
  stocked at JLCPCB must be sourced and consigned (CB: D7-D11, U11; radios: U1, ANT1).
- **Controlboard:** agree J15 (powerboard), J10 (kicker) and J4-J8 (motor modules: their connector is still PH 8P)
  pinouts with the mating boards; choose the OLED module; confirm the DotStar footprint (top-view drawing).
- **Radios:** decide the antenna (FXP831 5 GHz gain above the module's certified gain; Inboard WROOM-1 fallback sits
  over CB copper); fab notes for tented and plugged vias and the J2 paste-in-hole stencil; check the TPD4E05U06 land
  pattern against TI's drawing.

Fabrication outputs (gerbers, CPL) are not generated for the compact set; the BOMs are in each board's `bom/`.

## Interface rule

J9 / J2 and the standoff holes are shared by three projects. Change them in all three together and re-run the
mating check; see [docs/INTERFACE.md](docs/INTERFACE.md) §6.

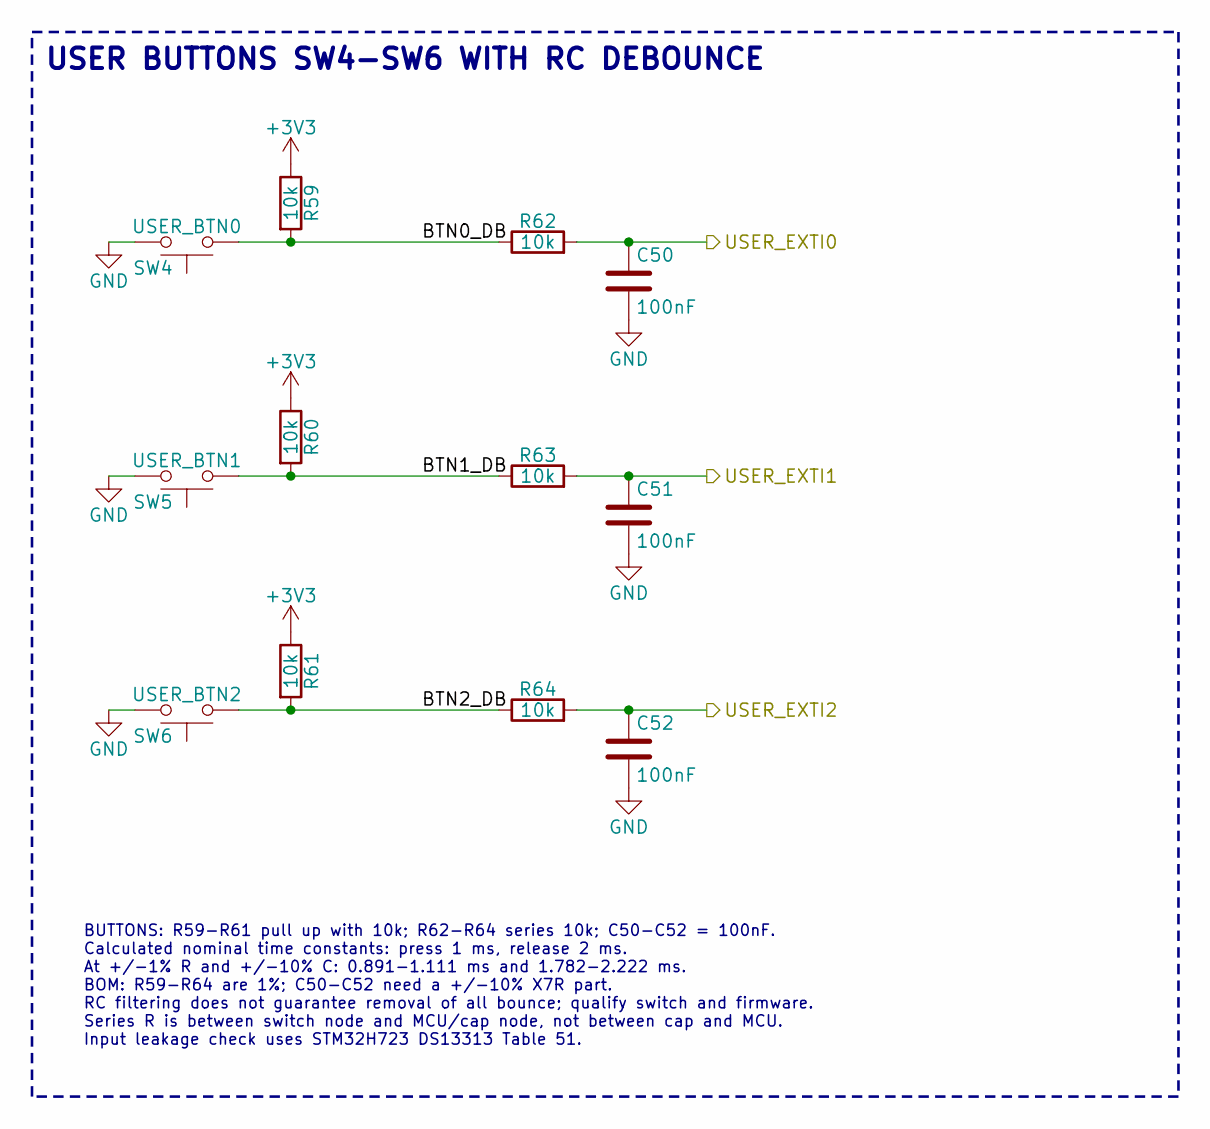
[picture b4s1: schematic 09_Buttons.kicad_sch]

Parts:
C50, C51, C52: 100nF; C_0402_1005Metric; Rating 16V X7R; MPN Samsung CL05B104KO5NNNC; LCSC C1525
R59, R60, R61, R62, R63, R64: 10k; R_0603_1608Metric; Rating 1%; MPN Panasonic ERJ-3EKF1002V; LCSC C25804
SW4: USER_BTN0; SW_PUSH_1P1T_6x3.5mm_H4.3_APEM_MJTP1243; MPN APEM MJTP1243; LCSC C2689636
SW5: USER_BTN1; SW_PUSH_1P1T_6x3.5mm_H4.3_APEM_MJTP1243; MPN APEM MJTP1243; LCSC C2689636
SW6: USER_BTN2; SW_PUSH_1P1T_6x3.5mm_H4.3_APEM_MJTP1243; MPN APEM MJTP1243; LCSC C2689636

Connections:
+3V3: R59.1, R60.1, R61.1; also elsewhere on the board
/MCU/USER_EXTI0: C50.1, R62.2; also elsewhere on the board
/MCU/USER_EXTI1: C51.1, R63.2; also elsewhere on the board
/MCU/USER_EXTI2: C52.1, R64.2; also elsewhere on the board
/User Buttons/BTN0_DB: R59.2, R62.1, SW4.1
/User Buttons/BTN1_DB: R60.2, R63.1, SW5.1
/User Buttons/BTN2_DB: R61.2, R64.1, SW6.1

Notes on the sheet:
BUTTONS: R59-R61 pull up with 10k; R62-R64 series 10k; C50-C52 = 100nF. Calculated nominal time constants: press 1 ms, release 2 ms. At +/-1% R and +/-10% C: 0.891-1.111 ms and 1.782-2.222 ms. BOM: R59-R64 are 1%; C50-C52 need a +/-10% X7R part. RC filtering does not guarantee removal of all bounce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
USER BUTTONS SW4-SW6 WITH RC DEBOUNCE

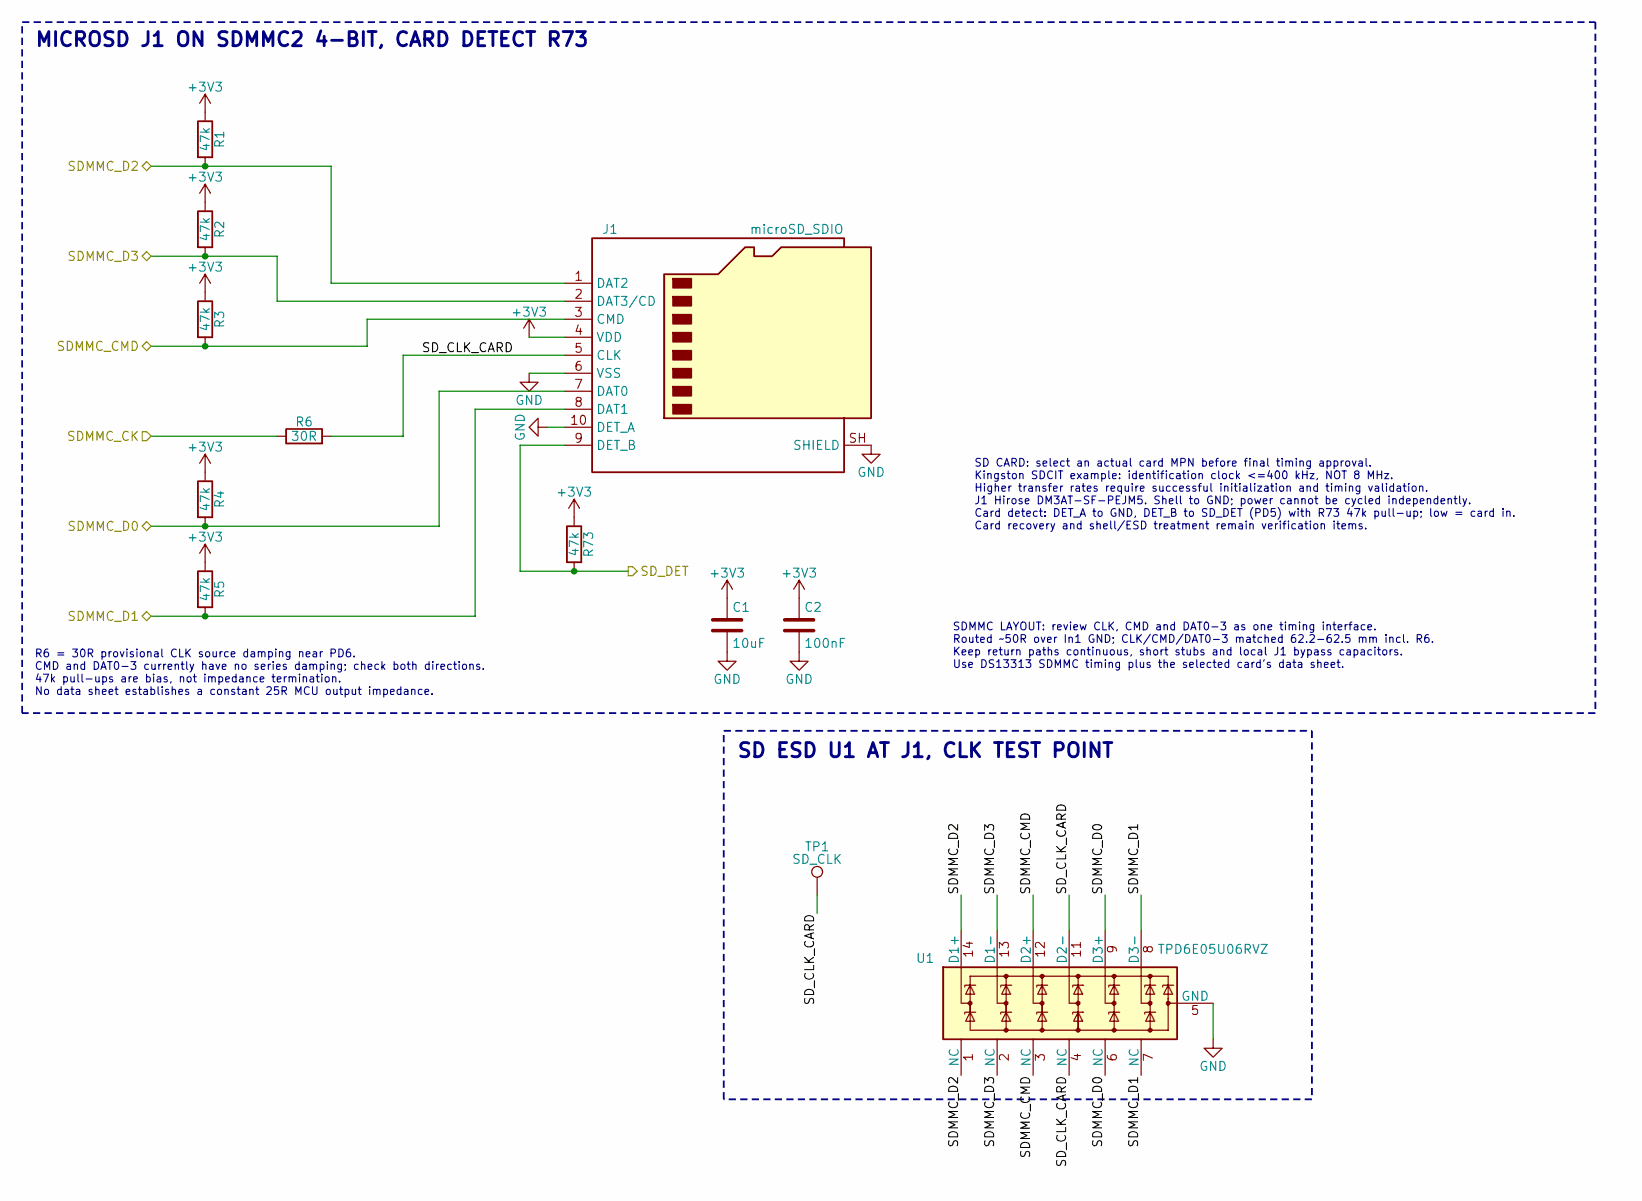
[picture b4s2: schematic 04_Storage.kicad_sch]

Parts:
C1: 10uF; C_0603_1608Metric; Rating 10V X5R 10%; MPN Taiyo Yuden LMK107BBJ106MALT; LCSC C19702
C2: 100nF; C_0402_1005Metric; Rating 16V X7R; MPN Samsung CL05B104KO5NNNC; LCSC C1525
J1: microSD_SDIO; microSD_HC_Hirose_DM3AT-SF-PEJM5; MPN Hirose DM3AT-SF-PEJM5; LCSC C114218
R1, R2, R3, R4, R5, R73: 47k; R_0402_1005Metric; Rating 1%; MPN Yageo RC0402FR-0747KL; LCSC C25792
R6: 30R; R_0402_1005Metric; Rating 1%; MPN Stackpole RMCF0402FT30R0; LCSC C2479340
TP1: SD_CLK; TestPoint_Pad_1.5x1.5mm
U1: TPD6E05U06RVZ; Texas_R-PUSON-N14; MPN TPD6E05U06RVZR; LCSC C962978

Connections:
+3V3: C1.1, C2.1, J1.4 (VDD), R1.1, R2.1, R3.1, R4.1, R5.1, R73.1; also elsewhere on the board
/MCU/SDMMC_CK: R6.1; also elsewhere on the board
/MCU/SD_DET: J1.9 (DET), R73.2; also elsewhere on the board
/SD Card Storage/SDMMC_CMD: J1.3 (CMD), R3.2, U1.3 (NC), U1.12 (D2+); also elsewhere on the board
/SD Card Storage/SDMMC_D0: J1.7 (DAT0), R4.2, U1.6 (NC), U1.9 (D3+); also elsewhere on the board
/SD Card Storage/SDMMC_D1: J1.8 (DAT1), R5.2, U1.7 (NC), U1.8 (D3-); also elsewhere on the board
/SD Card Storage/SDMMC_D2: J1.1 (DAT2), R1.2, U1.1 (NC), U1.14 (D1+); also elsewhere on the board
/SD Card Storage/SDMMC_D3: J1.2 (DAT3/CD), R2.2, U1.2 (NC), U1.13 (D1-); also elsewhere on the board
/SD Card Storage/SD_CLK_CARD: J1.5 (CLK), R6.2, TP1.1 (1_1), U1.4 (NC), U1.11 (D2-)

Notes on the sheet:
SD ESD U1 AT J1, CLK TEST POINT
MICROSD J1 ON SDMMC2 4-BIT, CARD DETECT R73
SDMMC LAYOUT: review CLK, CMD and DAT0-3 as one timing interface. Routed ~50R over In1 GND; CLK/CMD/DAT0-3 matched 62.2-62.5 mm incl. R6. Keep return paths continuous, short stubs and local J1 bypass capacitors. Use DS13313 SDMMC timing plus the selected card's data sheet.
SD CARD: select an actual card MPN before final timing approval. Kingston SDCIT example: identification clock <=400 kHz, NOT 8 MHz. Higher transfer rates require successful initialization and timing validation. J1 Hirose DM3AT-SF-PEJM5. Shell to GND; power cannot be cycled independently. Card detec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
R6 = 30R provisional CLK source damping near PD6. CMD and DAT0-3 currently have no series damping; check both directions. 47k pull-ups are bias, not impedance termination. No data sheet establishes a constant 25R MCU output impedance.
